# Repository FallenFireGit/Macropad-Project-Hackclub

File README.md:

# Macropad-Project-Hackclub

This project is a fully custom macropad created as part of Hack Club’s Blueprint program. It includes hardware design, firmware development, and key mapping to streamline workflows for coding, media control, and everyday tasks.

<br/>

## Final Design

<br/>

<br/>

## Schematic (Not the greatest schematic OAT, but it works)

<br/>

<br/>

## PCB

<br/>

<br/>

## Exploded View

Do note that the PCB is connected to the plate via an M2 screw (needed to be small to fit between switches), which screws into the plastic on the bottom plate. Since the switches are soldered to the PCB, the top plate is secured by being sandwiched between the MX switches and then the bottom plate. (The little red part for the OLED is held together with friction with the pins on the OLED. Once I actually get it, I will superglue it or use AMS in later revisions.)

<br/>

<br/>

## BOM

* 1x SEEEDUINO XIAO RP2040
* 4x MX Cherry Style switches
* 4x DSA Keycaps
* 1x EC11 Rotary Encoder
* 1x 0.91-inch OLED display
* 5x 1N4148 diodes
* 1x M2 Screw

## Firmware

The macropad runs [KMK](https://github.com/KMKfw/kmk_firmware) on CircuitPython. The board mounts as a USB drive, so edits take effect on save -- no toolchain, no compiling, no reflashing.

Four MX switches across two layers:

| Switch | Programming | CAD |
| --- | --- | --- |
| Top middle | `UP` | Ctrl+Z undo |
| Bottom middle | `DOWN` | Ctrl+Y redo |
| Bottom left | `LEFT` | `ESC` |
| Bottom right | `RIGHT` | `ENTER` |

The rotary encoder does triple duty:

| Encoder | Action |
| --- | --- |
| Turn | Volume, or menu navigation when a menu is open |
| Single click | Play / pause |
| Double click | Open the menu |

The menu holds a layer picker, a 25-minute Pomodoro timer, and a USB power indicator. Whenever nothing else needs the screen, the OLED loops a fire animation.

Pinout, install steps, and how to remap keys: [Firmware/circuitpython/README.md](Firmware/circuitpython/README.md)

<br/>

## Changing the OLED animation

[OLED Studio](Tools/README.md) turns any GIF or image into the format the display reads and copies it onto the board:

```bash
python Tools/oled_studio.py
```

Open a GIF, drag the threshold slider until the live preview looks right, then press **Send to macropad**. There is a command-line mode for scripting:

```bash
python Tools/oled_studio.py fire.gif --size 32x32 --dither --send
```

Needs Python 3.10+ and Pillow (`pip install pillow`).

<br/>

## Repository layout

| Path | Contents |
| --- | --- |
| `PCB/` | KiCad schematic and board layout |
| `CAD/` | Case model |
| `Production/` | Gerbers and printable plates |
| `Firmware/circuitpython/` | The firmware running on the board, and its animation |
| `Tools/` | OLED Studio, the animation uploader |

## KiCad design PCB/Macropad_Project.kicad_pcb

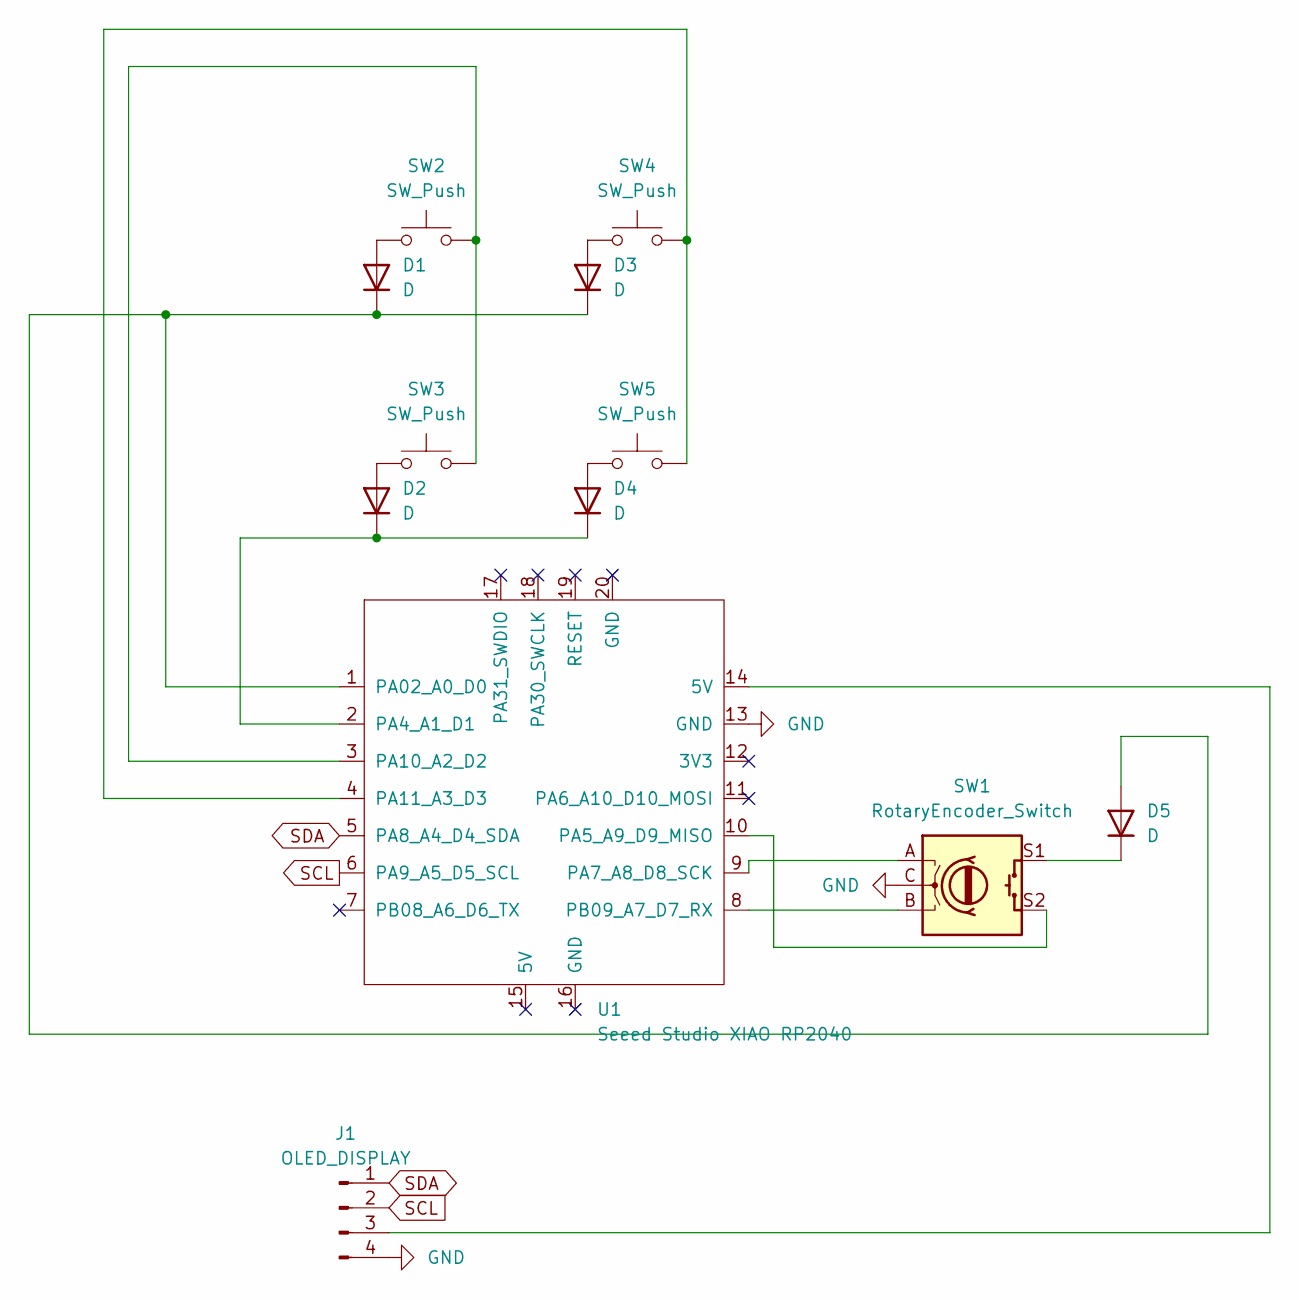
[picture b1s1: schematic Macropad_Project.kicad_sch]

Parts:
D1, D2, D3, D4, D5: D; D_DO-35_SOD27_P7.62mm_Horizontal
J1: OLED_DISPLAY; PinHeader_1x04_P2.54mm_Vertical
SW1: RotaryEncoder_Switch; RotaryEncoder_Alps_EC11E-Switch_Vertical_H20mm
SW2, SW3, SW4, SW5: SW_Push; MX-Solderable-1U
U1: Seeed Studio XIAO RP2040; XIAO-Generic-Hybrid-14P-2.54-21X17.8MM

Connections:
GND: J1.4, SW1.C, U1.13 (GND)
unnamed: D1.2 (A), SW2.1
unnamed: D1.1 (K), D3.1 (K), D5.2 (A), U1.1 (PA02_A0_D0)
unnamed: D2.2 (A), SW3.1
unnamed: D2.1 (K), D4.1 (K), U1.2 (PA4_A1_D1)
unnamed: D3.2 (A), SW4.1
unnamed: D4.2 (A), SW5.1
unnamed: D5.1 (K), SW1.S1
unnamed: J1.3, U1.14 (5V)
unnamed: SW1.S2, U1.10 (PA5_A9_D9_MISO)
unnamed: SW1.A, U1.9 (PA7_A8_D8_SCK)
unnamed: SW2.2, SW3.2, U1.3 (PA10_A2_D2)
unnamed: SW4.2, SW5.2, U1.4 (PA11_A3_D3)
unnamed: SW1.B, U1.8 (PB09_A7_D7_RX)
SCL: J1.2, U1.6 (PA9_A5_D5_SCL)
SDA: J1.1, U1.5 (PA8_A4_D4_SDA)

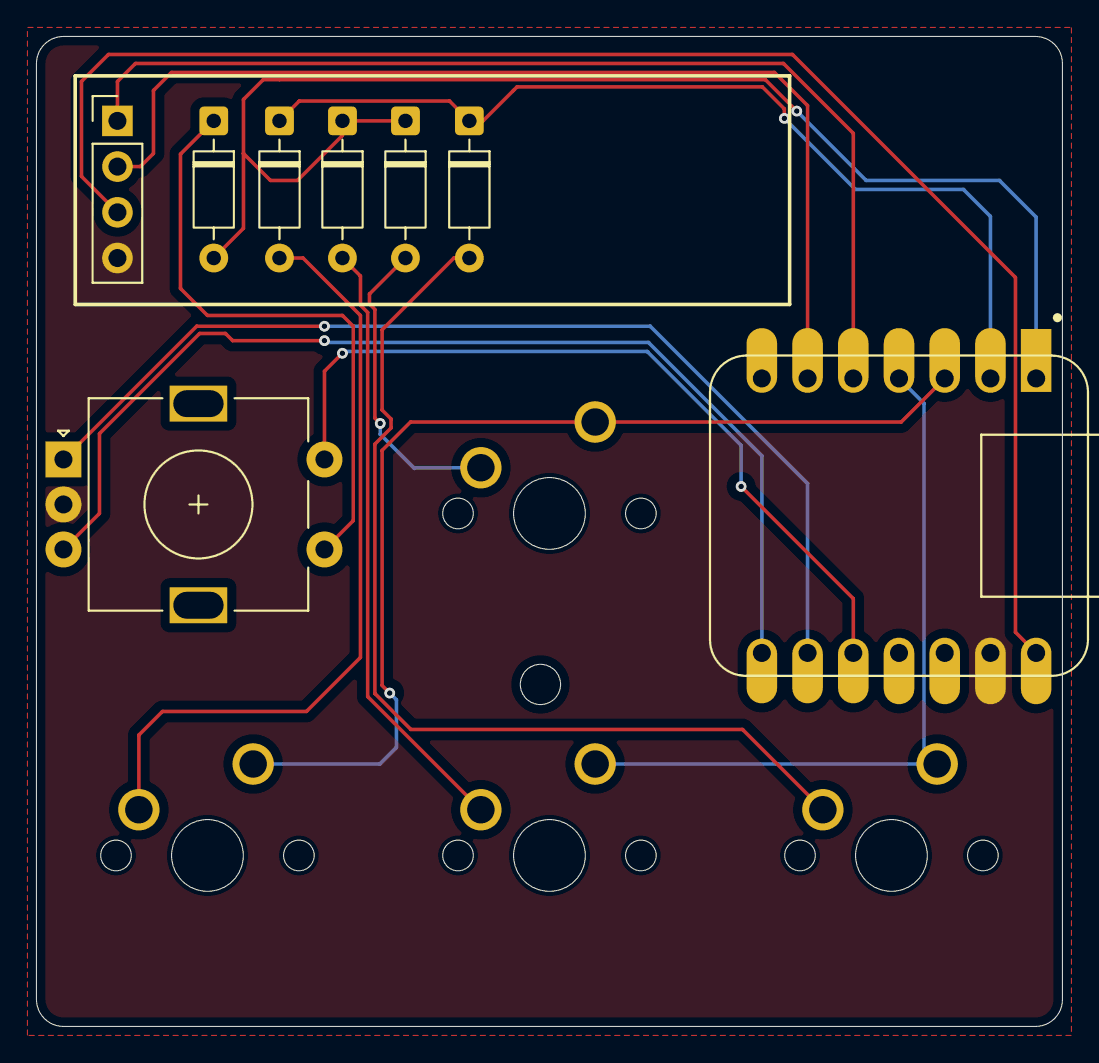
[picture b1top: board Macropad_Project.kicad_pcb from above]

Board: 2 copper layers, 57.0 x 55.0 mm, 12 parts (0 on the bottom side), 16 nets.

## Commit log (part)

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2026-03-29 Create Macropad-Blueprint-CAD
2026-03-30 Rename gerber.zip to Production/gerber.zip
2026-03-30 Rename Bottom Plate.step to Production/Bottom Plate.step
2026-03-30 Rename OLED Plate.step to Production/OLED Plate.step
2026-03-30 Rename Top Plate.step to Production/Top Plate.step
2026-03-30 Rename macropad_project_default.uf2 to Production/macropad_project_default.uf2
